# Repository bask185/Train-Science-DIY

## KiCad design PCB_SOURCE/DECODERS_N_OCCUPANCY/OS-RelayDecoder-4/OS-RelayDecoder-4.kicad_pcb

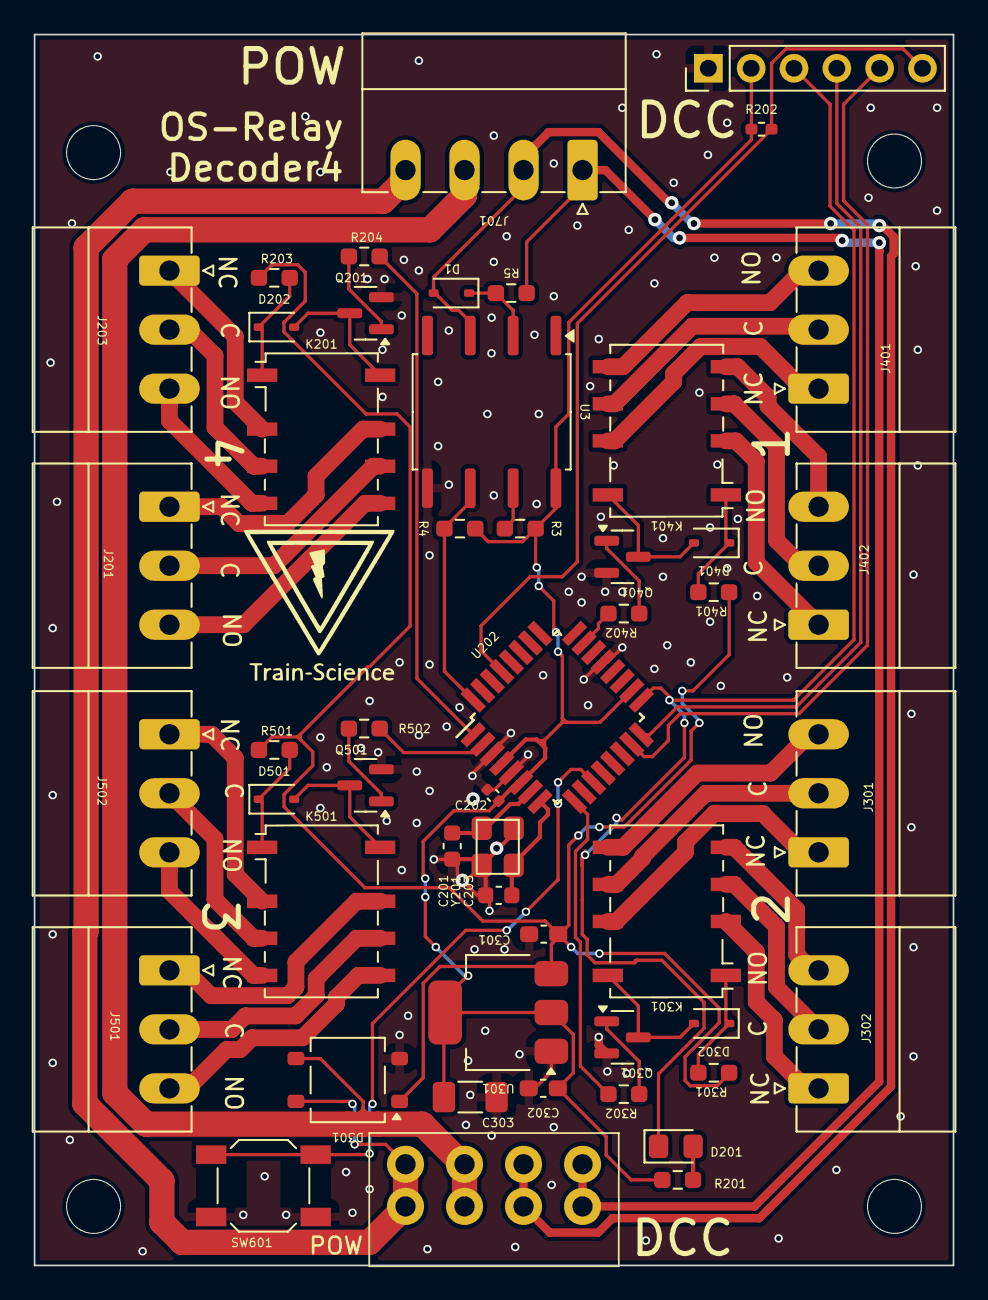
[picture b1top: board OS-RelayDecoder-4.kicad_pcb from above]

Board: 2 copper layers, 54.5 x 73.0 mm, 54 parts (0 on the bottom side), 58 nets.

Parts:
C201, C203: 12pF; C_0603_1608Metric
C202: 100nF; C_0402_1005Metric
C301: 330nF; C_0603_1608Metric_Pad1.08x0.95mm_HandSolder
C302: 100nF; C_0603_1608Metric_Pad1.08x0.95mm_HandSolder
C303: 100uF; C_1206_3216Metric_Pad1.33x1.80mm_HandSolder
D1: D; D_SOD-323
D201: LED; LED_0805_2012Metric_Pad1.15x1.40mm_HandSolder
D202, D302, D401, D501: 1N4148WS; D_SOD-323
D301: MB10S; TO-269AA
H101, H102, H103, H104: MountingHole; MountingHole_3.2mm_M3
J201, J203, J301, J302, J401, J402, J501, J502: PhoenixContact_MC_1,5_3-G-3.5_1x03_P3.50mm_Horizontal
J202: ICSP; PinHeader_1x06_P2.54mm_Vertical
J701: FEMALE; PhoenixContact_MC_1,5_4-G-3.5_1x04_P3.50mm_Horizontal
J702: MALE; connector_3.50mm_4P horizontal_MALE
K201, K301, K401, K501: G6K-2F-Y-TR DC12; Relay_DPDT_Omron_G6K-2F-Y
Q201, Q301, Q401, Q501: NPN_TOR; SOT-23
R3, R4: 10k; R_0603_smalltext
R5: 1k5; R_0603_smalltext
R201: 6k2; R_0603_1608Metric_Pad0.98x0.95mm_HandSolder
R202: 10k; R_0402_1005Metric_Pad0.72x0.64mm_HandSolder
R203, R301, R401, R501: 100R; R_0603_smalltext
R204, R302, R402, R502: 1k; R_0603_smalltext
SW601: default_switch
U3: 6N137; SOP-8_6.62x9.15mm_P2.54mm
U202: ATmega328-A; TQFP-32_7x7mm_P0.8mm
U301: AMS1117-5.0; SOT-223-3_TabPin2
Y201: Crystal_GND2; crystal_arduino

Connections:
+5V: C202.1, C302.1, C303.1, J202.2, R3.1, R4.1, R201.1, R202.1, U3.8 (VCC), U202.4 (VCC), U202.6 (VCC), U202.18 (AVCC), U301.2 (VO)
/DCC+power/DCC: R4.2, U3.6 (VO), U202.32 (PD2)
/DCC+power/DCC_A: J701.1, J702.1, R5.1
/DCC+power/DCC_B: D1.2 (A), J701.2, J702.2, U3.3 (C)
/DCC+power/P1: D301.4, J701.4, J702.4
/DCC+power/P2: D301.3, J701.3, J702.3
/MCU/LED: D201.1 (K), J202.3, U202.17 (PB5)
/MCU/MISO: J202.4, U202.16 (PB4)
/MCU/MOSI: J202.5, U202.15 (PB3)
/MCU/Reset: J202.6, R202.2, U202.29 (~RESET/PC6)
/MCU/X1: C201.2, U202.7 (XTAL1/PB6), Y201.1
/MCU/X2: C203.2, U202.8 (XTAL2/PB7), Y201.3
/MCU/coil1: R204.2, U202.1 (PD3)
/MCU/coil2: R302.2, U202.9 (PD5)
/MCU/coil3: R402.2, U202.23 (PC0)
/MCU/coil4: R502.2, U202.2 (PD4)
GND: C201.1, C202.2, C203.1, C301.2, C302.2, C303.2, D301.2 (-), J202.1, Q201.2 (E), Q301.2 (E), Q401.2 (E), Q501.2 (E), SW601.1 (A), U3.5 (GND), U202.3 (GND), U202.5 (GND), U202.21 (GND), U301.1 (GND), Y201.2 (GND), Y201.4 (GND)
unnamed: D1.1 (K), R5.2, U3.2 (A)
unnamed: D201.2 (A), R201.2
unnamed: D202.2 (A), K201.8, Q201.3 (C)
unnamed: D202.1 (K), K201.1, R203.2
unnamed: D302.2 (A), K301.8, Q301.3 (C)
unnamed: D302.1 (K), K301.1, R301.2
unnamed: D401.2 (A), K401.8, Q401.3 (C)
unnamed: D401.1 (K), K401.1, R401.2
unnamed: D501.2 (A), K501.8, Q501.3 (C)
unnamed: D501.1 (K), K501.1, R501.2
unnamed: J201.1, K201.7
unnamed: J201.2, K201.6
unnamed: J201.3, K201.5
unnamed: J203.1, K201.2
unnamed: J203.2, K201.3
unnamed: J203.3, K201.4
unnamed: J301.1, K301.7
unnamed: J301.2, K301.6
unnamed: J301.3, K301.5
unnamed: J302.1, K301.2
unnamed: J302.2, K301.3
unnamed: J302.3, K301.4
unnamed: J401.1, K401.7
unnamed: J401.2, K401.6
unnamed: J401.3, K401.5
unnamed: J402.1, K401.2
unnamed: J402.2, K401.3
unnamed: J402.3, K401.4
unnamed: J501.1, K501.7
unnamed: J501.2, K501.6
unnamed: J501.3, K501.5
unnamed: J502.1, K501.2
unnamed: J502.2, K501.3
unnamed: J502.3, K501.4
unnamed: Q201.1 (B), R204.1
unnamed: Q301.1 (B), R302.1
unnamed: Q401.1 (B), R402.1
unnamed: Q501.1 (B), R502.1
unnamed: SW601.2 (B), U202.11 (PD7)
unnamed: R3.2, U3.7 (EN)
VCC: C301.1, D301.1 (+), R203.1, R301.1, R401.1, R501.1, U301.3 (VI)

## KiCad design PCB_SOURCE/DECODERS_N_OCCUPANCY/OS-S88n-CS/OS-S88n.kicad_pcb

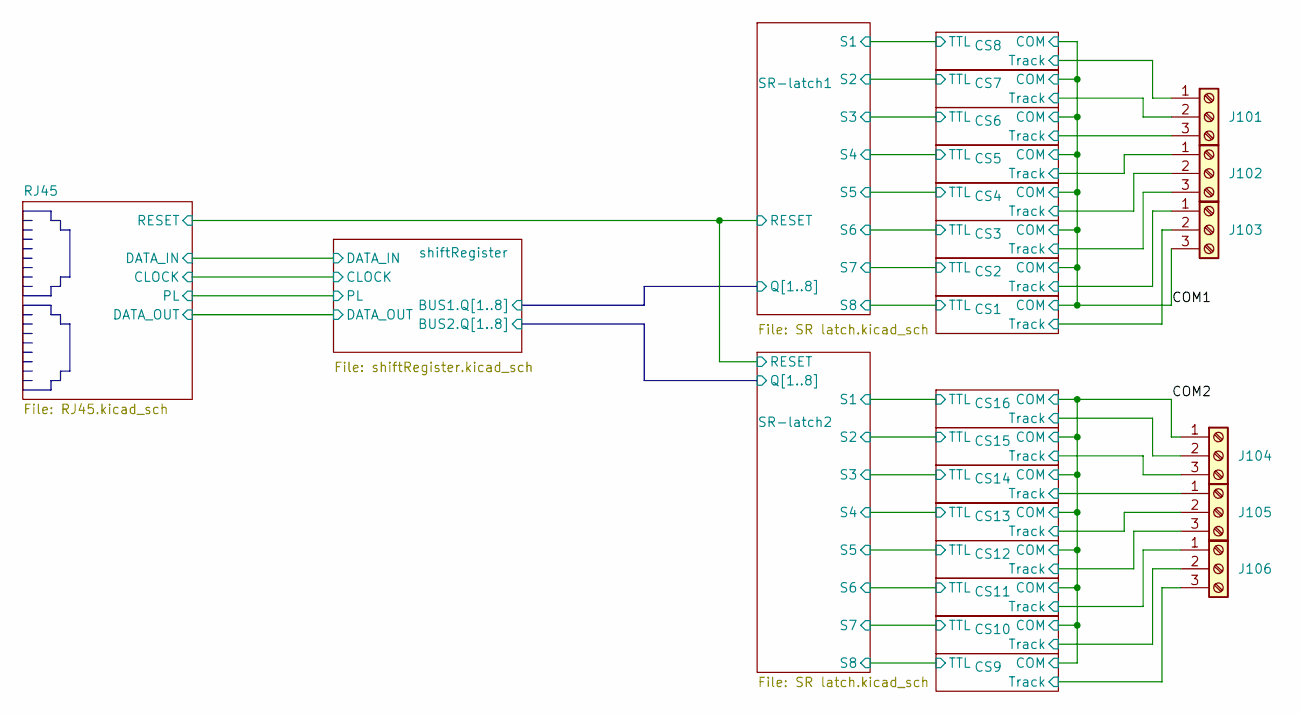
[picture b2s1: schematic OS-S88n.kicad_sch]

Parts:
J101, J102, J103, J104, J105, J106: Screw_Terminal_01x03; TerminalBlock_Phoenix_MKDS-1,5-3-5.08_1x03_P5.08mm_Horizont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; JLCPCB Part# C557666

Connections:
/COM1: J103.3; also elsewhere on the board
/COM2: J104.1; also elsewhere on the board
/CS1/Track: J103.2; also elsewhere on the board
/CS2/Track: J103.1; also elsewhere on the board
/CS3/Track: J102.3; also elsewhere on the board
/CS4/Track: J102.2; also elsewhere on the board
/CS5/Track: J102.1; also elsewhere on the board
/CS6/Track: J101.3; also elsewhere on the board
/CS7/Track: J101.2; also elsewhere on the board
/CS8/Track: J101.1; also elsewhere on the board
/CS9/Track: J106.3; also elsewhere on the board
/CS10/Track: J106.2; also elsewhere on the board
/CS11/Track: J106.1; also elsewhere on the board
/CS12/Track: J105.3; also elsewhere on the board
/CS13/Track: J105.2; also elsewhere on the board
/CS14/Track: J105.1; also elsewhere on the board
/CS15/Track: J104.3; also elsewhere on the board
/CS16/Track: J104.2; also elsewhere on the board

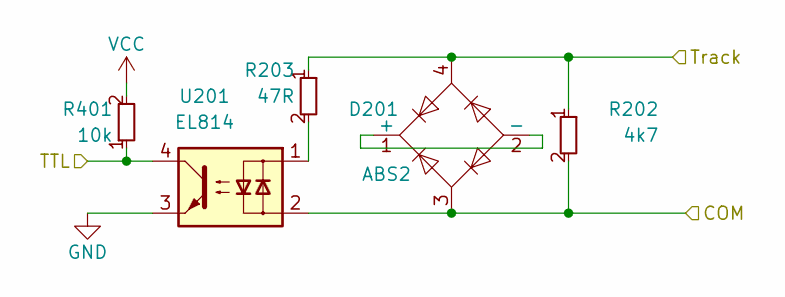
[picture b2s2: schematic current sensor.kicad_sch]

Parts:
D201: ABS2; Diode_Bridge_Diotec_ABS; JLCPCB Part# C123897
R202: 4k7; R_0603_smalltext; JLCPCB Part# C23162
R203: 47R; R_0603_smalltext; JLCPCB Part# C23182
R401: 10k; R_0603_smalltext; JLCPCB Part# C25804
U201: EL814; SMDIP-4_W9.53mm; JLCPCB Part# C500388

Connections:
/COM1: D201.3, R202.2, U201.2; also elsewhere on the board
/CS1/Track: D201.4, R202.1, R203.1; also elsewhere on the board
unnamed: D201.1 (+), D201.2 (-)
unnamed: R203.2, U201.1

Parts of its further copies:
D401, D501, D601, D701, D801, D901, D1001, D1101, D1301, D1401, D1501, D1601, D1701, D1801, D1901: ABS2; Diode_Bridge_Diotec_ABS; JLCPCB Part# C123897
R201, R501, R601, R701, R801, R901, R1001, R1101, R1301, R1401, R1501, R1601, R1701, R1801, R1901: 10k; R_0603_smalltext; JLCPCB Part# C25804
R402, R502, R602, R702, R802, R902, R1002, R1102, R1302, R1402, R1502, R1602, R1702, R1802, R1902: 4k7; R_0603_smalltext; JLCPCB Part# C23162
R403, R503, R603, R703, R803, R903, R1003, R1103, R1303, R1403, R1503, R1603, R1703, R1803, R1903: 47R; R_0603_smalltext; JLCPCB Part# C23182
U401, U501, U601, U701, U801, U901, U1001, U1101, U1301, U1401, U1501, U1601, U1701, U1801, U1901: EL814; SMDIP-4_W9.53mm; JLCPCB Part# C500388

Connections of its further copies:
/COM1: D401.3, D501.3, D601.3, D701.3, D801.3, D901.3, D1001.3, R402.2, R502.2, R602.2, R702.2, R802.2, R902.2, R1002.2, U401.2, U501.2, U601.2, U701.2, U801.2, U901.2, U1001.2; also elsewhere on the board
/COM2: D1101.3, D1301.3, D1401.3, D1501.3, D1601.3, D1701.3, D1801.3, D1901.3, R1102.2, R1302.2, R1402.2, R1502.2, R1602.2, R1702.2, R1802.2, R1902.2, U1101.2, U1301.2, U1401.2, U1501.2, U1601.2, U1701.2, U1801.2, U1901.2; also elsewhere on the board
/CS2/Track: D401.4, R402.1, R403.1; also elsewhere on the board
/CS3/TTL: R501.1, U501.4; also elsewhere on the board
/CS3/Track: D501.4, R502.1, R503.1; also elsewhere on the board
/CS4/TTL: R601.1, U601.4; also elsewhere on the board
/CS4/Track: D601.4, R602.1, R603.1; also elsewhere on the board
/CS5/TTL: R701.1, U701.4; also elsewhere on the board
/CS5/Track: D701.4, R702.1, R703.1; also elsewhere on the board
/CS6/TTL: R801.1, U801.4; also elsewhere on the board
/CS6/Track: D801.4, R802.1, R803.1; also elsewhere on the board
/CS7/TTL: R901.1, U901.4; also elsewhere on the board
/CS7/Track: D901.4, R902.1, R903.1; also elsewhere on the board
/CS8/TTL: R1001.1, U1001.4; also elsewhere on the board
/CS8/Track: D1001.4, R1002.1, R1003.1; also elsewhere on the board
/CS9/TTL: R1101.1, U1101.4; also elsewhere on the board
/CS9/Track: D1101.4, R1102.1, R1103.1; also elsewhere on the board
/CS10/TTL: R1301.1, U1301.4; also elsewhere on the board
/CS10/Track: D1301.4, R1302.1, R1303.1; also elsewhere on the board
/CS11/TTL: R1401.1, U1401.4; also elsewhere on the board
/CS11/Track: D1401.4, R1402.1, R1403.1; also elsewhere on the board
/CS12/TTL: R1501.1, U1501.4; also elsewhere on the board
/CS12/Track: D1501.4, R1502.1, R1503.1; also elsewhere on the board
/CS13/TTL: R1601.1, U1601.4; also elsewhere on the board
/CS13/Track: D1601.4, R1602.1, R1603.1; also elsewhere on the board
/CS14/TTL: R1701.1, U1701.4; also elsewhere on the board
/CS14/Track: D1701.4, R1702.1, R1703.1; also elsewhere on the board
/CS15/TTL: R1801.1, U1801.4; also elsewhere on the board
/CS15/Track: D1801.4, R1802.1, R1803.1; also elsewhere on the board
/CS16/TTL: R1901.1, U1901.4; also elsewhere on the board
/CS16/Track: D1901.4, R1902.1, R1903.1; also elsewhere on the board
unnamed: D401.1 (+), D401.2 (-)
unnamed: D501.1 (+), D501.2 (-)
unnamed: D601.1 (+), D601.2 (-)
unnamed: D701.1 (+), D701.2 (-)
unnamed: D801.1 (+), D801.2 (-)
unnamed: D901.1 (+), D901.2 (-)
unnamed: D1001.1 (+), D1001.2 (-)
unnamed: D1101.1 (+), D1101.2 (-)
unnamed: D1301.1 (+), D1301.2 (-)
unnamed: D1401.1 (+), D1401.2 (-)
unnamed: D1501.1 (+), D1501.2 (-)
unnamed: D1601.1 (+), D1601.2 (-)
unnamed: D1701.1 (+), D1701.2 (-)
unnamed: D1801.1 (+), D1801.2 (-)
unnamed: D1901.1 (+), D1901.2 (-)
unnamed: R403.2, U401.1
unnamed: R503.2, U501.1
unnamed: R603.2, U601.1
unnamed: R703.2, U701.1
unnamed: R803.2, U801.1
unnamed: R903.2, U901.1
unnamed: R1003.2, U1001.1
unnamed: R1103.2, U1101.1
unnamed: R1303.2, U1301.1
unnamed: R1403.2, U1401.1
unnamed: R1503.2, U1501.1
unnamed: R1603.2, U1601.1
unnamed: R1703.2, U1701.1
unnamed: R1803.2, U1801.1
unnamed: R1903.2, U1901.1

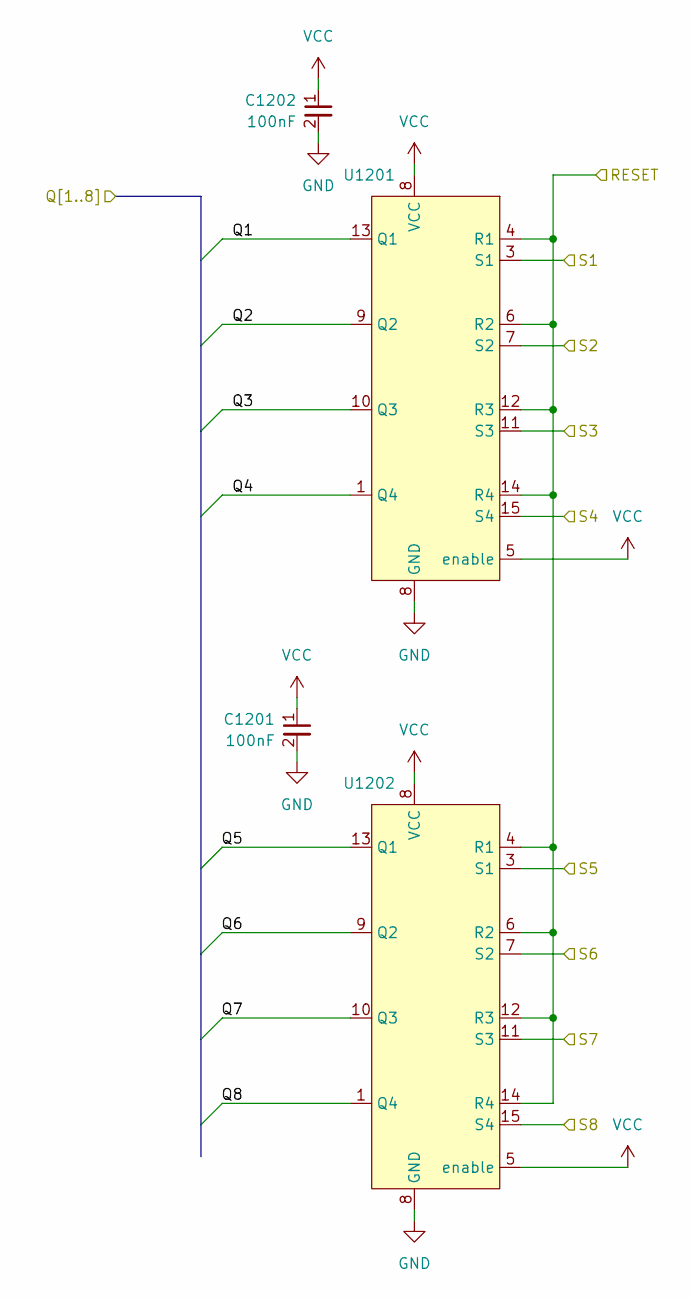
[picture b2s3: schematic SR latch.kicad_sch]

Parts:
C1201, C1202: 100nF; C_0402_1005Metric; JLCPCB Part# C307331
U1201, U1202: SOIC-16_3.9x9.9mm_P1.27mm; JLCPCB Part# C133986

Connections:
/CS9/TTL: U1202.15 (S4); also elsewhere on the board
/CS10/TTL: U1202.11 (S3); also elsewhere on the board
/CS11/TTL: U1202.7 (S2); also elsewhere on the board
/CS12/TTL: U1202.3 (S1); also elsewhere on the board
/CS13/TTL: U1201.15 (S4); also elsewhere on the board
/CS14/TTL: U1201.11 (S3); also elsewhere on the board
/CS15/TTL: U1201.7 (S2); also elsewhere on the board
/CS16/TTL: U1201.3 (S1); also elsewhere on the board
/RJ45/RESET: U1201.4 (R1), U1201.6 (R2), U1201.12 (R3), U1201.14 (R4), U1202.4 (R1), U1202.6 (R2), U1202.12 (R3), U1202.14 (R4); also elsewhere on the board
/SR-latch2/Q1: U1201.13 (Q1); also elsewhere on the board
/SR-latch2/Q2: U1201.9 (Q2); also elsewhere on the board
/SR-latch2/Q3: U1201.10 (Q3); also elsewhere on the board
/SR-latch2/Q4: U1201.1 (Q4); also elsewhere on the board
/SR-latch2/Q5: U1202.13 (Q1); also elsewhere on the board
/SR-latch2/Q6: U1202.9 (Q2); also elsewhere on the board
/SR-latch2/Q7: U1202.10 (Q3); also elsewhere on the board
/SR-latch2/Q8: U1202.1 (Q4); also elsewhere on the board

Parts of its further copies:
C301, C302: 100nF; C_0402_1005Metric; JLCPCB Part# C307331
U301, U302: SOIC-16_3.9x9.9mm_P1.27mm; JLCPCB Part# C133986

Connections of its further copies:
/CS3/TTL: U302.7 (S2); also elsewhere on the board
/CS4/TTL: U302.3 (S1); also elsewhere on the board
/CS5/TTL: U301.15 (S4); also elsewhere on the board
/CS6/TTL: U301.11 (S3); also elsewhere on the board
/CS7/TTL: U301.7 (S2); also elsewhere on the board
/CS8/TTL: U301.3 (S1); also elsewhere on the board
/RJ45/RESET: U301.4 (R1), U301.6 (R2), U301.12 (R3), U301.14 (R4), U302.4 (R1), U302.6 (R2), U302.12 (R3), U302.14 (R4); also elsewhere on the board
/SR-latch1/Q1: U301.13 (Q1); also elsewhere on the board
/SR-latch1/Q2: U301.9 (Q2); also elsewhere on the board
/SR-latch1/Q3: U301.10 (Q3); also elsewhere on the board
/SR-latch1/Q4: U301.1 (Q4); also elsewhere on the board
/SR-latch1/Q5: U302.13 (Q1); also elsewhere on the board
/SR-latch1/Q6: U302.9 (Q2); also elsewhere on the board
/SR-latch1/Q7: U302.10 (Q3); also elsewhere on the board
/SR-latch1/Q8: U302.1 (Q4); also elsewhere on the board

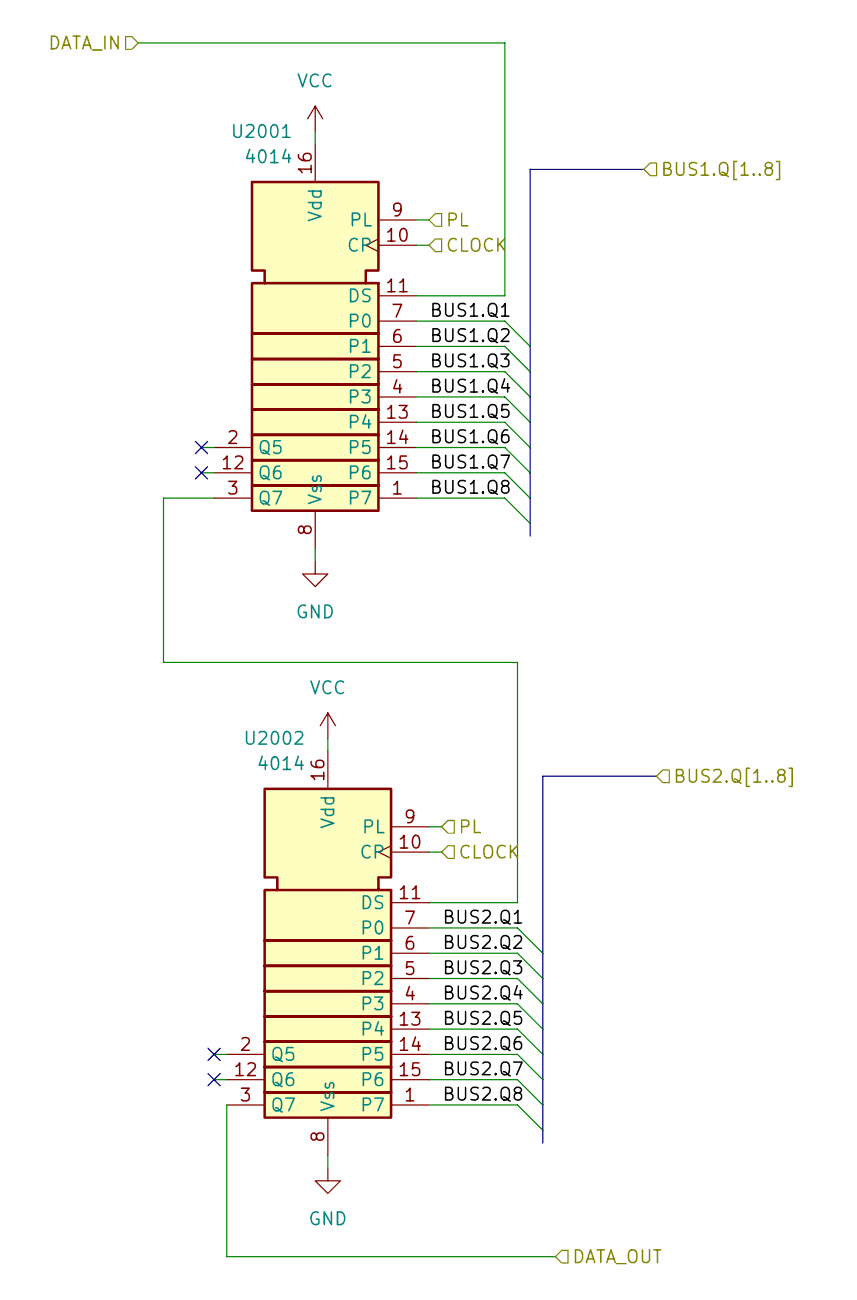
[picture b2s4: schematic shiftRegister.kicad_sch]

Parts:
U2001, U2002: 4014; SOIC-16_3.9x9.9mm_P1.27mm; JLCPCB Part# C496106

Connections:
/RJ45/CLOCK: U2001.10 (CP), U2002.10 (CP); also elsewhere on the board
/RJ45/DATA_IN: U2001.11 (DS); also elsewhere on the board
/RJ45/DATA_OUT: U2002.3 (Q7); also elsewhere on the board
/RJ45/PL: U2001.9 (PL), U2002.9 (PL); also elsewhere on the board
/SR-latch1/Q1: U2001.7 (P0); also elsewhere on the board
/SR-latch1/Q2: U2001.6 (P1); also elsewhere on the board
/SR-latch1/Q3: U2001.5 (P2); also elsewhere on the board
/SR-latch1/Q4: U2001.4 (P3); also elsewhere on the board
/SR-latch1/Q5: U2001.13 (P4); also elsewhere on the board
/SR-latch1/Q6: U2001.14 (P5); also elsewhere on the board
/SR-latch1/Q7: U2001.15 (P6); also elsewhere on the board
/SR-latch1/Q8: U2001.1 (P7); also elsewhere on the board
/SR-latch2/Q1: U2002.7 (P0); also elsewhere on the board
/SR-latch2/Q2: U2002.6 (P1); also elsewhere on the board
/SR-latch2/Q3: U2002.5 (P2); also elsewhere on the board
/SR-latch2/Q4: U2002.4 (P3); also elsewhere on the board
/SR-latch2/Q5: U2002.13 (P4); also elsewhere on the board
/SR-latch2/Q6: U2002.14 (P5); also elsewhere on the board
/SR-latch2/Q7: U2002.15 (P6); also elsewhere on the board
/SR-latch2/Q8: U2002.1 (P7); also elsewhere on the board
unnamed: U2001.3 (Q7), U2002.11 (DS)

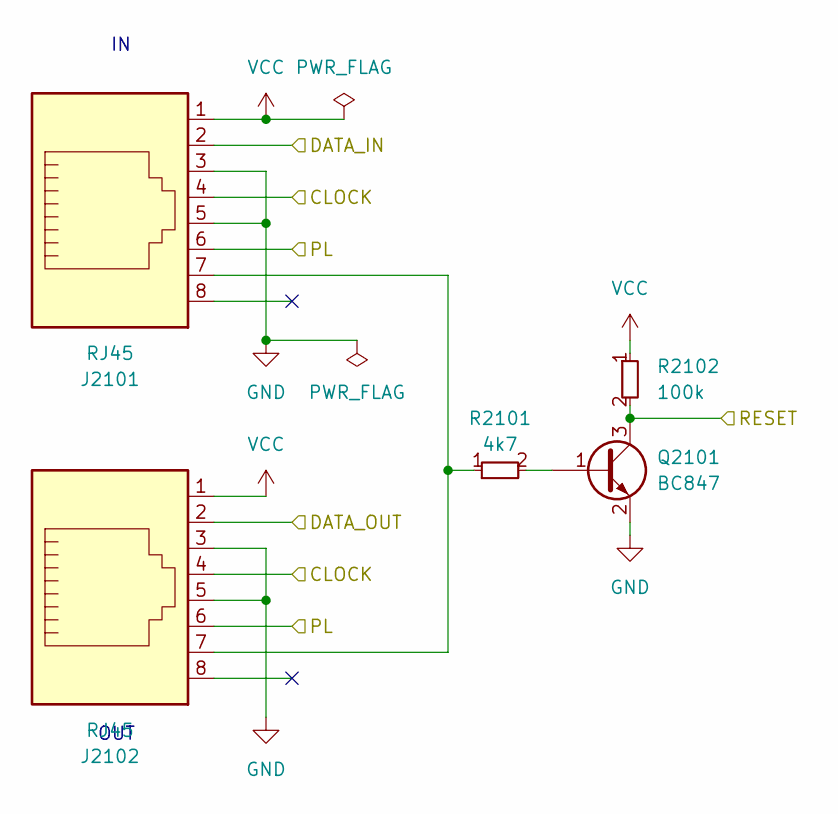
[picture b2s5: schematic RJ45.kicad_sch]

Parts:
J2101, J2102: RJ45; RJ45_Amphenol_54602-x08_Horizontal; JLCPCB Part# C2847314
Q2101: BC847; SOT-23; JLCPCB Part# C181140
R2101: 4k7; R_0603_smalltext; JLCPCB Part# C23162
R2102: 100k; R_0603_smalltext; JLCPCB Part# C25803

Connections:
/RJ45/CLOCK: J2101.4, J2102.4; also elsewhere on the board
/RJ45/DATA_IN: J2101.2; also elsewhere on the board
/RJ45/DATA_OUT: J2102.2; also elsewhere on the board
/RJ45/PL: J2101.6, J2102.6; also elsewhere on the board
/RJ45/RESET: Q2101.3 (C), R2102.2; also elsewhere on the board
unnamed: J2101.7, J2102.7, R2101.1
unnamed: Q2101.1 (B), R2101.2

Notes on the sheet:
OUT

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
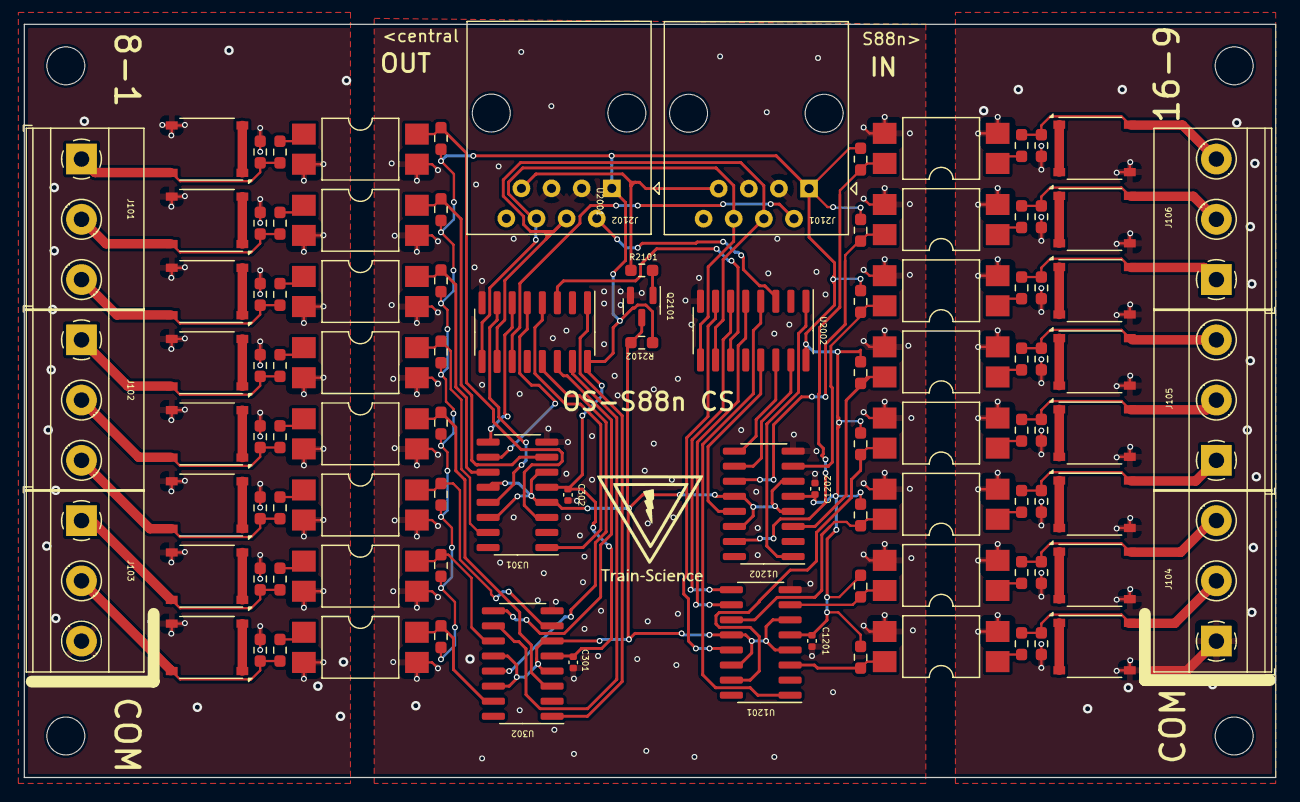
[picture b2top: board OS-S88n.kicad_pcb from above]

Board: 2 copper layers, 105.5 x 63.5 mm, 101 parts (0 on the bottom side), 92 nets.

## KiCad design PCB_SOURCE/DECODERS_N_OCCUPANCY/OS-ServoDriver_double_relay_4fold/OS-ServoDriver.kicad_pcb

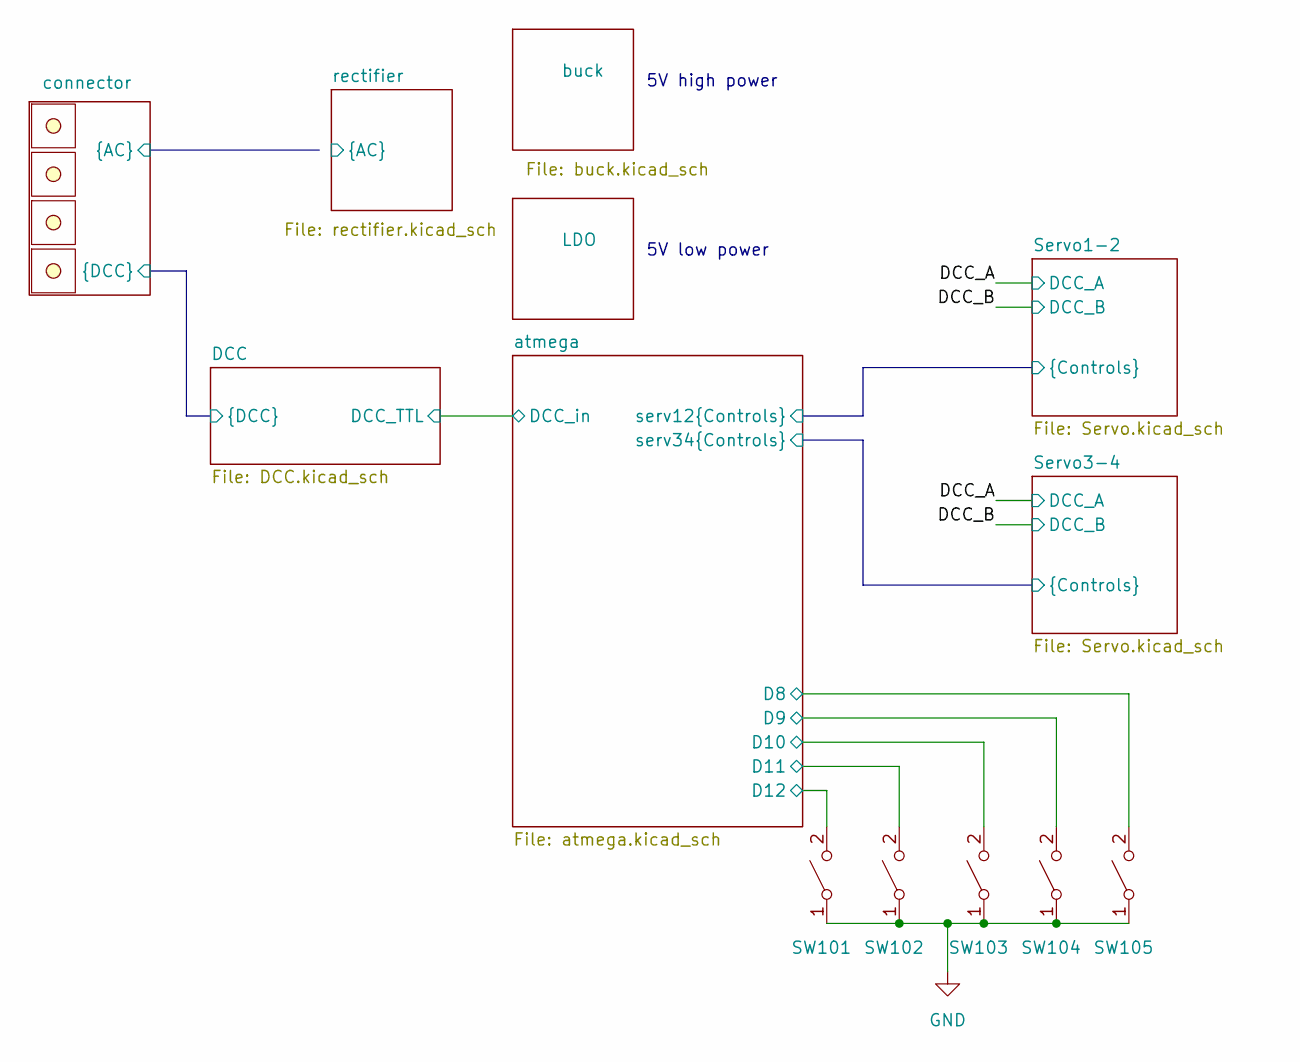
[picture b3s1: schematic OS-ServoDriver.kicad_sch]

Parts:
SW101, SW102, SW103, SW104, SW105: default_switch; JLCPCB Part# C318884

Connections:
/atmega/D8: SW105.2 (B); also elsewhere on the board
/atmega/D9: SW104.2 (B); also elsewhere on the board
/atmega/D10: SW103.2 (B); also elsewhere on the board
/atmega/MISO: SW101.2 (B); also elsewhere on the board
/atmega/MOSI: SW102.2 (B); also elsewhere on the board

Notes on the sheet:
5V high power
5V low power

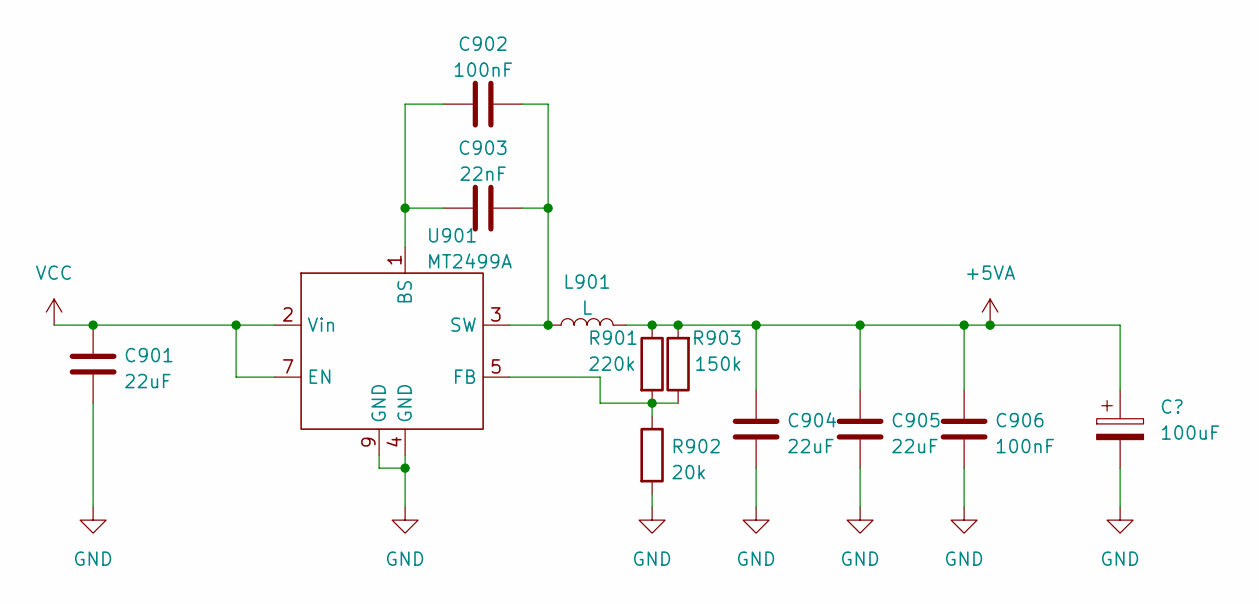
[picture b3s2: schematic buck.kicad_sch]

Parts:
C901, C904, C905: 22uF; C_0603_1608Metric; JLCPCB Part# C45783
C902, C906: 100nF; C_0402_1005Metric; JLCPCB Part# C307331
C903: 22nF; C_0402_1005Metric; JLCPCB Part# C1729
L901: L; L_Bourns-SRU8028_8.0x8.0mm; JLCPCB Part# C2929438
R901: 220k; R_0603_1608Metric; JLCPCB Part# C22961
R902: 20k; R_0603_1608Metric; JLCPCB Part# C4328
R903: 150k; R_0603_1608Metric; JLCPCB Part# C22807
U901: MT2499A; TI_SO-PowerPAD-8; JLCPCB Part# C3007555

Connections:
+5VA: C904.1, C905.1, C906.1, L901.2, R901.1, R903.2; also elsewhere on the board
unnamed: C902.1, C903.1, U901.1 (BS)
unnamed: R901.2, R902.1, R903.1, U901.5 (FB)
unnamed: C902.2, C903.2, L901.1, U901.3 (SW)
VCC: C901.1, U901.2 (Vin), U901.7 (EN); also elsewhere on the board

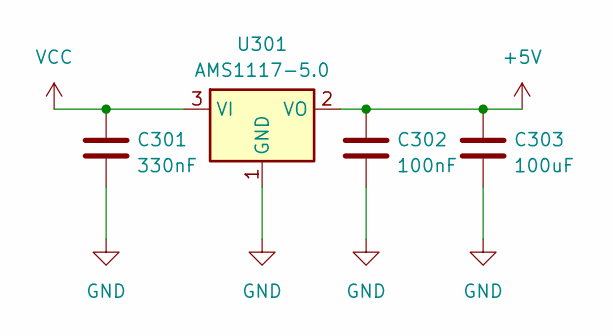
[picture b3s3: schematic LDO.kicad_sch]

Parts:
C301: 330nF; C_0603_1608Metric_Pad1.08x0.95mm_HandSolder; JLCPCB Part# C1615
C302: 100nF; C_0603_1608Metric_Pad1.08x0.95mm_HandSolder; JLCPCB Part# C14663
C303: 100uF; C_1206_3216Metric_Pad1.33x1.80mm_HandSolder; JLCPCB Part# C15008
U301: AMS1117-5.0; SOT-223-3_TabPin2; JLCPCB Part# C6187

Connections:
VCC: C301.1, U301.3 (IN); also elsewhere on the board

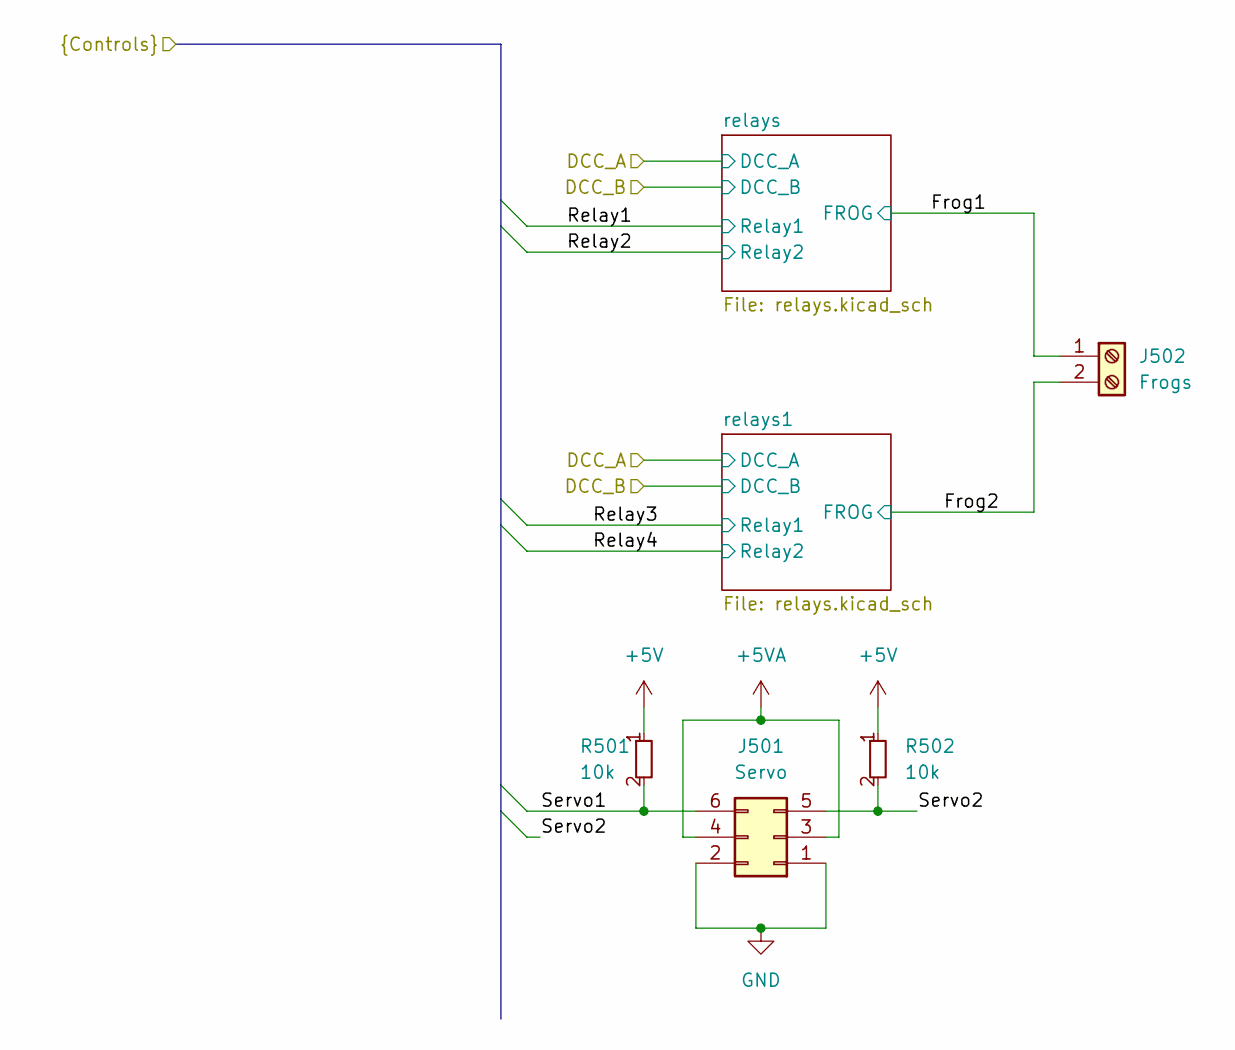
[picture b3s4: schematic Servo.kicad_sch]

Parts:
J501: Servo; PinHeader_2x03_P2.54mm_Vertical
J502: Frogs; TerminalBlock_Phoenix_MKDS-1,5-2-5.08_1x02_P5.08mm_Horizont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
R501, R502: 10k; R_0603_smalltext; JLCPCB Part# C25804

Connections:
+5VA: J501.3, J501.4; also elsewhere on the board
/Servo1-2/Frog1: J502.1; also elsewhere on the board
/Servo1-2/Frog2: J502.2; also elsewhere on the board
/Servo1-2/Servo1: J501.6, R501.2; also elsewhere on the board
/Servo1-2/Servo2: J501.5, R502.2; also elsewhere on the board

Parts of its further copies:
J701: Servo; PinHeader_2x03_P2.54mm_Vertical
J702: Frogs; TerminalBlock_Phoenix_MKDS-1,5-2-5.08_1x02_P5.08mm_Horizont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
R704, R705: 10k; R_0603_smalltext; JLCPCB Part# C25804

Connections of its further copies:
+5VA: J701.3, J701.4; also elsewhere on the board
/Servo3-4/Frog1: J702.1; also elsewhere on the board
/Servo3-4/Frog2: J702.2; also elsewhere on the board
/Servo3-4/Servo1: J701.6, R704.2; also elsewhere on the board
/Servo3-4/Servo2: J701.5, R705.2; also elsewhere on the board

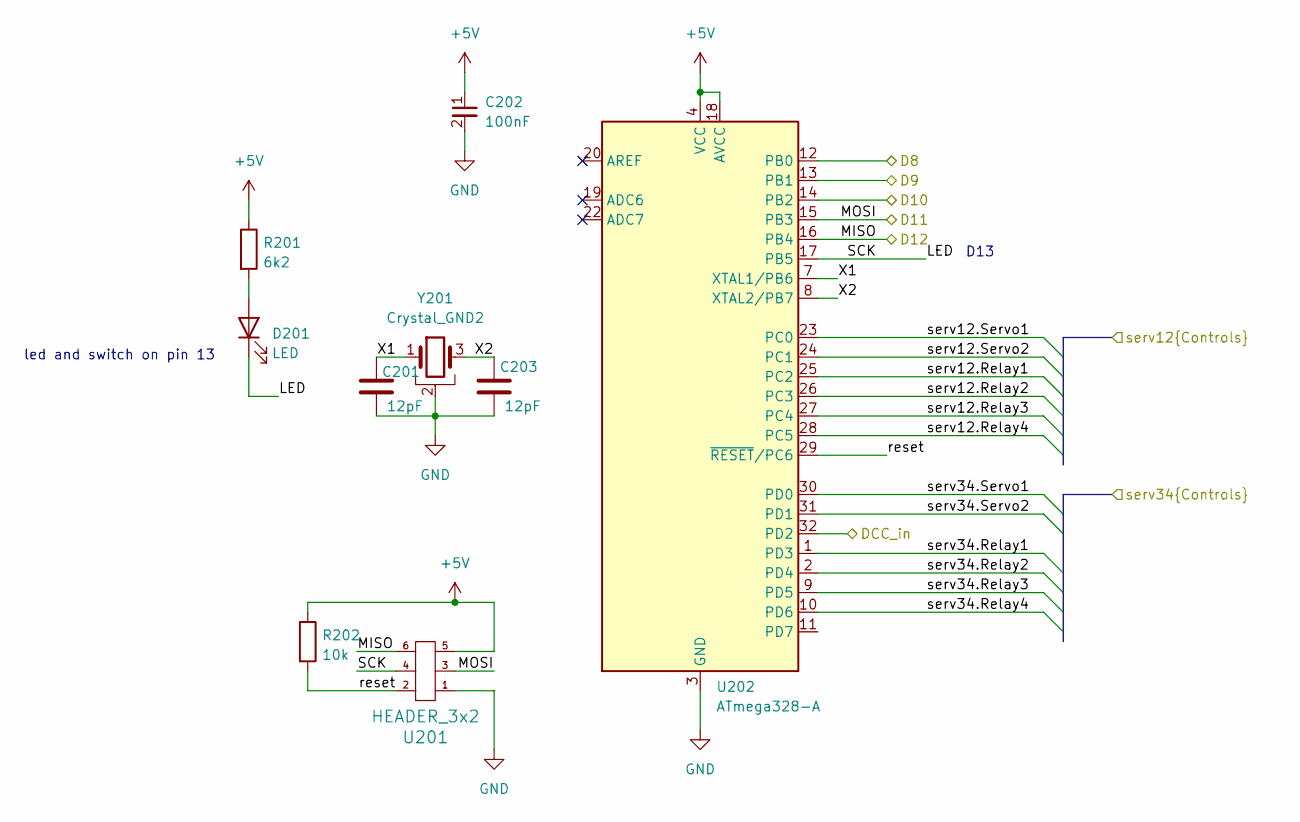
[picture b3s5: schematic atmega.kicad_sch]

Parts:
C201, C203: 12pF; C_0603_1608Metric; JLCPCB Part# C38523
C202: 100nF; C_0402_1005Metric; JLCPCB Part# C307331
D201: LED; LED_0805_2012Metric_Pad1.15x1.40mm_HandSolder; JLCPCB Part# C84256
R201: 6k2; R_0603_1608Metric_Pad0.98x0.95mm_HandSolder; JLCPCB Part# C4260
R202: 10k; R_0402_1005Metric_Pad0.72x0.64mm_HandSolder; JLCPCB Part# C25744
U201: HEADER_3x2; PinSocket_2x03_P1.27mm_Vertical
U202: ATmega328-A; TQFP-32_7x7mm_P0.8mm; JLCPCB Part# C14877
Y201: Crystal_GND2; crystal_arduino; JLCPCB Part# C13738

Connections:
/DCC/DCC_TTL: U202.32 (PD2); also elsewhere on the board
/Servo1-2/Relay1: U202.25 (PC2); also elsewhere on the board
/Servo1-2/Relay2: U202.26 (PC3); also elsewhere on the board
/Servo1-2/Relay3: U202.27 (PC4); also elsewhere on the board
/Servo1-2/Relay4: U202.28 (PC5); also elsewhere on the board
/Servo1-2/Servo1: U202.23 (PC0); also elsewhere on the board
/Servo1-2/Servo2: U202.24 (PC1); also elsewhere on the board
/Servo3-4/Relay1: U202.1 (PD3); also elsewhere on the board
/Servo3-4/Relay2: U202.2 (PD4); also elsewhere on the board
/Servo3-4/Relay3: U202.9 (PD5); also elsewhere on the board
/Servo3-4/Relay4: U202.10 (PD6); also elsewhere on the board
/Servo3-4/Servo1: U202.30 (PD0); also elsewhere on the board
/Servo3-4/Servo2: U202.31 (PD1); also elsewhere on the board
/atmega/A6: U202.19 (ADC6)
/atmega/A7: U202.22 (ADC7)
/atmega/D8: U202.12 (PB0); also elsewhere on the board
/atmega/D9: U202.13 (PB1); also elsewhere on the board
/atmega/D10: U202.14 (PB2); also elsewhere on the board
/atmega/LED: D201.1 (K), U201.4, U202.17 (PB5)
/atmega/MISO: U201.6, U202.16 (PB4); also elsewhere on the board
/atmega/MOSI: U201.3, U202.15 (PB3); also elsewhere on the board
/atmega/X1: C201.2, U202.7 (XTAL1/PB6), Y201.1
/atmega/X2: C203.2, U202.8 (XTAL2/PB7), Y201.3
/atmega/reset: R202.2, U201.2, U202.29 (~RESET/PC6)
unnamed: D201.2 (A), R201.2

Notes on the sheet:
led and switch on pin 13
D13

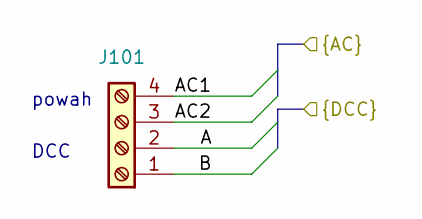
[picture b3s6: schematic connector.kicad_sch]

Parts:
J101: Screw_Terminal_01x04; TerminalBlock_Phoenix_MKDS-1,5-4-5.08_1x04_P5.08mm_Horizont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

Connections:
/DCC_A: J101.2; also elsewhere on the board
/DCC_B: J101.1; also elsewhere on the board
unnamed 41: J101.3; also elsewhere on the board
unnamed 42: J101.4; also elsewhere on the board

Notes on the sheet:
DCC
powah

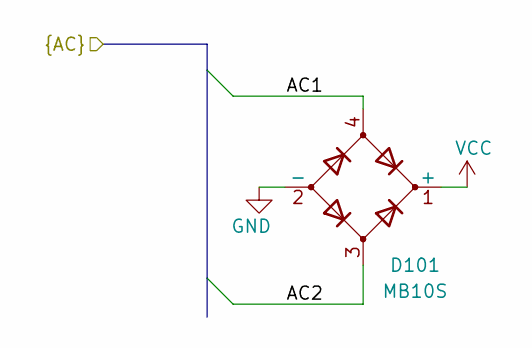
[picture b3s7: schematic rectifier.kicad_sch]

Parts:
D101: MB10S; TO-269AA; JLCPCB Part# C2488

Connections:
unnamed 41: D101.3; also elsewhere on the board
unnamed 42: D101.4; also elsewhere on the board
VCC: D101.1 (+); also elsewhere on the board
